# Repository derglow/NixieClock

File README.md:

# NixieClock

This repository contains the files used to make my nixie clock design. I designed the PCBs, the laser cut acrylic, and wrote the code.

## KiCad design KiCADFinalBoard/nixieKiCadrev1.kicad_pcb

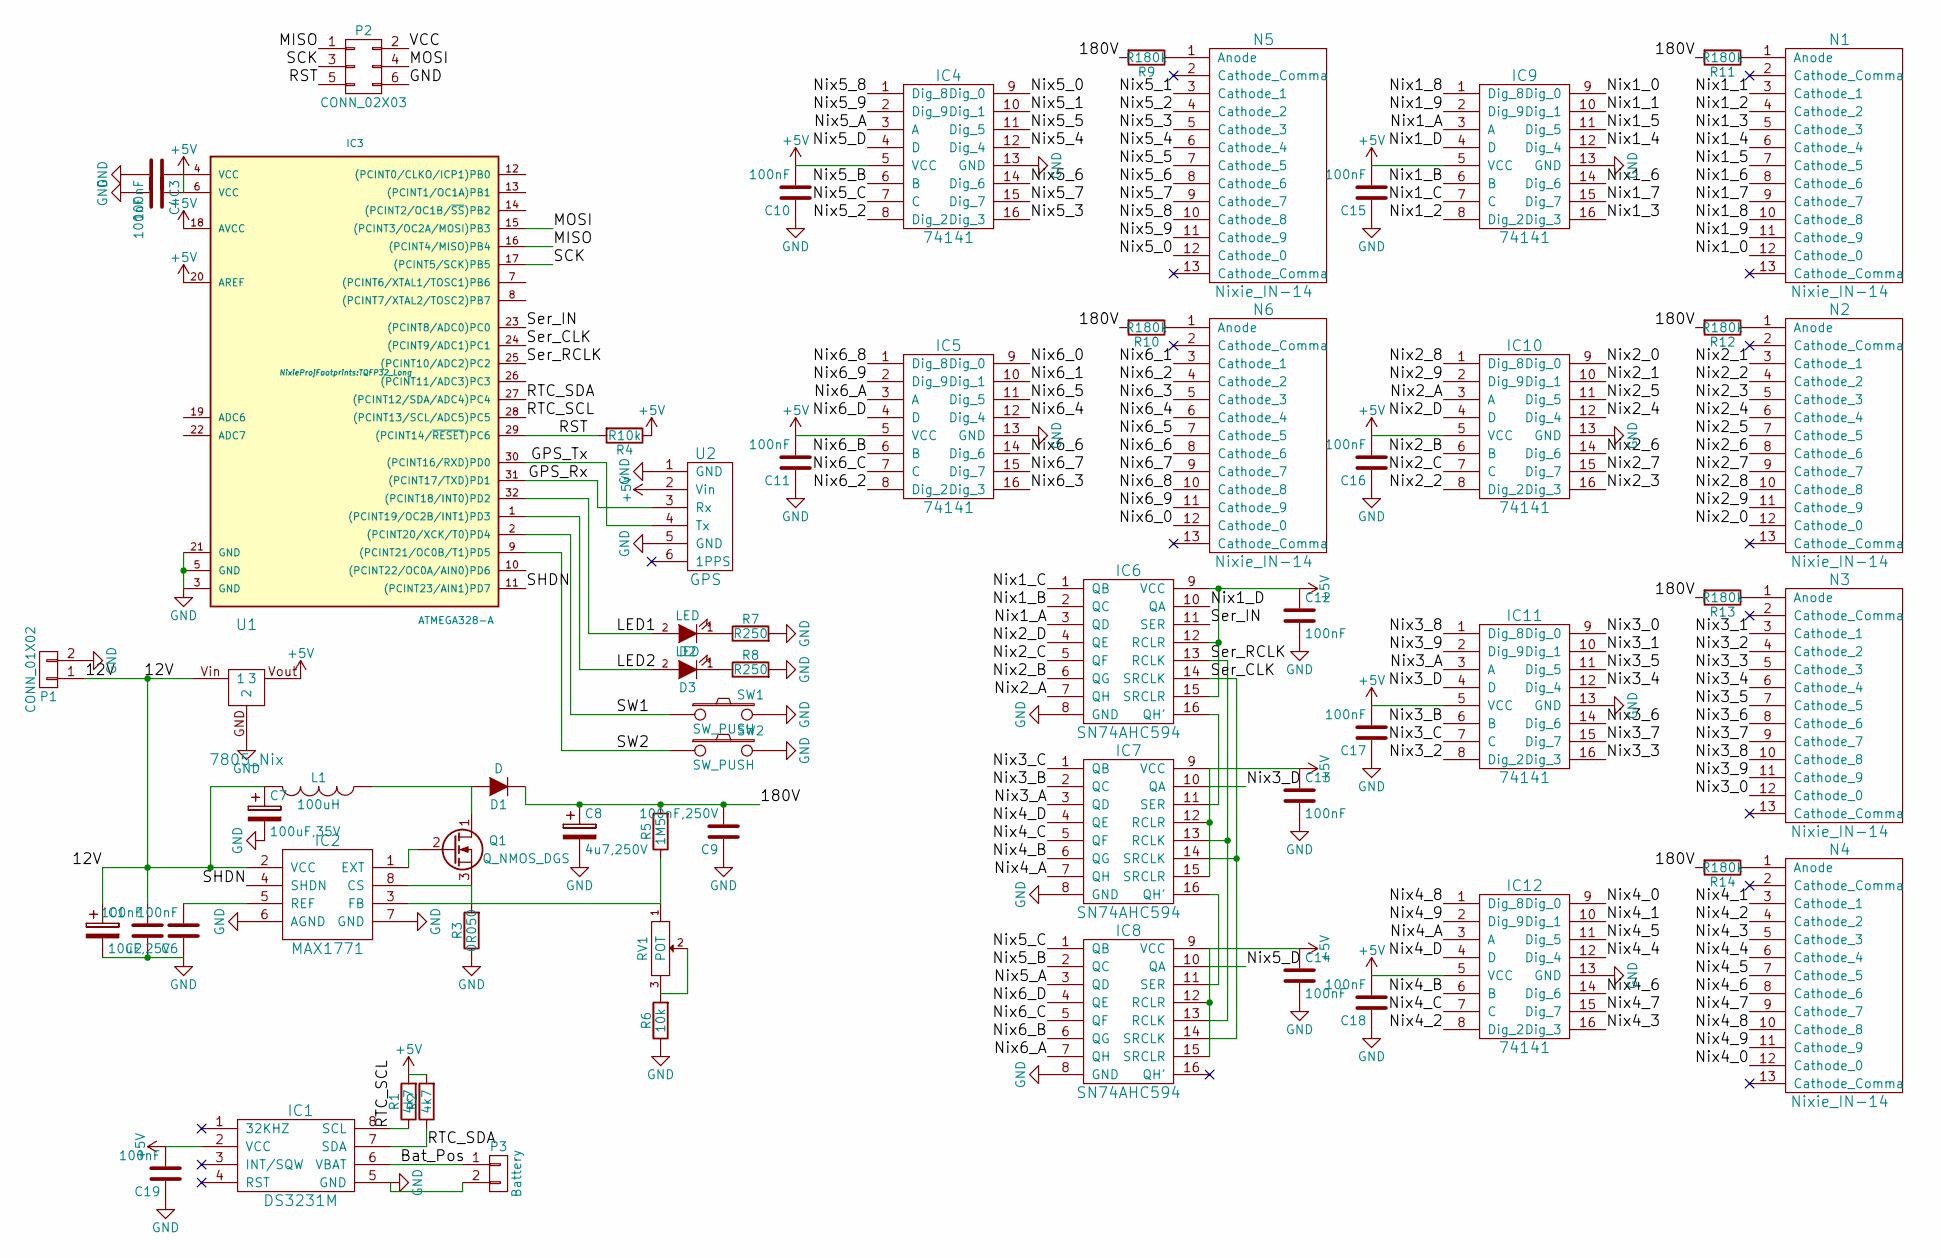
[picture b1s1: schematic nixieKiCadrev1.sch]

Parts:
C1: 10uF,25V; TantalC_SizeC_EIA-6032_HandSoldering
C2, C3, C4, C6, C10, C11, C12, C13, C14, C15, C16, C17, C18, C19: 100nF; C_0805_HandSoldering
C7: 100uF,35V; TantalC_SizeE_EIA-7360_HandSoldering
C8: 4u7,250V; c_elec_10x10
C9: 100nF,250V; C_2220_HandSoldering
D1: D; Diode-MELF_Handsoldering
D2, D3: LED; LED-0805
IC1: DS3231M; SOIC-8-N
IC2: MAX1771; SOIC-8-N
IC3: ATMEGA328-A; TQFP32_Long
IC4, IC5, IC9, IC10, IC11, IC12: 74141; DIP-16_W7.62mm_LongPads
IC6, IC7, IC8: SN74AHC594; TSSOP-16_4.4x5mm_Pitch0.65mm
L1: 100uH; Inductor
N1, N2, N3, N4, N5, N6: Nixie_IN-14; Nixie_IN14
P1: CONN_01X02; BARREL_JACK
P2: CONN_02X03; Pin_Header_Straight_2x03
P3: Battery; CR2032_BatHolder
Q1: Q_NMOS_DGS; TO-220_Neutral123_Vertical
R1, R2: 4k7; R_0805_HandSoldering
R3: 0R050; R_2512_HandSoldering
R4: R10k; R_0805_HandSoldering
R5: 1M5; R_2512_HandSoldering
R6: 10k; R_0805_HandSoldering
R7, R8: R250; R_0805_HandSoldering
R9, R10, R11, R12, R13, R14: R180k; R_0805_HandSoldering
RV1: POT; TrimPot
SW1, SW2: SW_PUSH; SW_SPST_PTS645
U1: 7805_Nix; TO-220_Neutral123_Vertical
U2: GPS; EM406gps

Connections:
+5V: C3.1, C4.1, C10.2, C11.2, C12.1, C13.1, C14.1, C15.2, C16.2, C17.2, C18.2, C19.2, IC1.2 (VCC), IC3.4 (VCC), IC3.6 (VCC), IC3.18 (AVCC), IC3.20 (AREF), IC4.5 (VCC), IC5.5 (VCC), IC6.9 (VCC), IC6.12 (RCLR), IC6.15 (SRCLR), IC7.9 (VCC), IC7.12 (RCLR), IC7.15 (SRCLR), IC8.9 (VCC), IC8.12 (RCLR), IC8.15 (SRCLR), IC9.5 (VCC), IC10.5 (VCC), IC11.5 (VCC), IC12.5 (VCC), R1.2, R2.2, R4.1, U1.3, U1.Vout (3), U2.2 (Vin)
/12V: C1.1, C2.2, C7.1, IC2.2 (VCC), L1.2, P1.1, U1.1, U1.Vin (1)
/180V: C8.1, C9.2, D1.1 (K), R5.2, R9.2, R10.2, R11.2, R12.2, R13.2, R14.2
/Bat_Pos: IC1.6 (VBAT), P3.1
/GPS_Rx: IC3.31 ((PCINT17/TXD)PD1), U2.3 (Rx)
/GPS_Tx: IC3.30 ((PCINT16/RXD)PD0), U2.4 (Tx)
/LED1: D2.2 (A), IC3.32 ((PCINT18/INT0)PD2)
/LED2: D3.2 (A), IC3.1 ((PCINT19/OC2B/INT1)PD3)
/MISO: IC3.16 ((PCINT4/MISO)PB4), P2.1
/MOSI: IC3.15 ((PCINT3/OC2A/MOSI)PB3), P2.4
/Nix1_0: IC9.9 (Dig_0), N1.12 (Cathode_0)
/Nix1_1: IC9.10 (Dig_1), N1.3 (Cathode_1)
/Nix1_2: IC9.8 (Dig_2), N1.4 (Cathode_2)
/Nix1_3: IC9.16 (Dig_3), N1.5 (Cathode_3)
/Nix1_4: IC9.12 (Dig_4), N1.6 (Cathode_4)
/Nix1_5: IC9.11 (Dig_5), N1.7 (Cathode_5)
/Nix1_6: IC9.14 (Dig_6), N1.8 (Cathode_6)
/Nix1_7: IC9.15 (Dig_7), N1.9 (Cathode_7)
/Nix1_8: IC9.1 (Dig_8), N1.10 (Cathode_8)
/Nix1_9: IC9.2 (Dig_9), N1.11 (Cathode_9)
/Nix1_A: IC6.3 (QD), IC9.3 (A)
/Nix1_B: IC6.2 (QC), IC9.6 (B)
/Nix1_C: IC6.1 (QB), IC9.7 (C)
/Nix1_D: IC6.10 (QA), IC9.4 (D)
/Nix2_0: IC10.9 (Dig_0), N2.12 (Cathode_0)
/Nix2_1: IC10.10 (Dig_1), N2.3 (Cathode_1)
/Nix2_2: IC10.8 (Dig_2), N2.4 (Cathode_2)
/Nix2_3: IC10.16 (Dig_3), N2.5 (Cathode_3)
/Nix2_4: IC10.12 (Dig_4), N2.6 (Cathode_4)
/Nix2_5: IC10.11 (Dig_5), N2.7 (Cathode_5)
/Nix2_6: IC10.14 (Dig_6), N2.8 (Cathode_6)
/Nix2_7: IC10.15 (Dig_7), N2.9 (Cathode_7)
/Nix2_8: IC10.1 (Dig_8), N2.10 (Cathode_8)
/Nix2_9: IC10.2 (Dig_9), N2.11 (Cathode_9)
/Nix2_A: IC6.7 (QH), IC10.3 (A)
/Nix2_B: IC6.6 (QG), IC10.6 (B)
/Nix2_C: IC6.5 (QF), IC10.7 (C)
/Nix2_D: IC6.4 (QE), IC10.4 (D)
/Nix3_0: IC11.9 (Dig_0), N3.12 (Cathode_0)
/Nix3_1: IC11.10 (Dig_1), N3.3 (Cathode_1)
/Nix3_2: IC11.8 (Dig_2), N3.4 (Cathode_2)
/Nix3_3: IC11.16 (Dig_3), N3.5 (Cathode_3)
/Nix3_4: IC11.12 (Dig_4), N3.6 (Cathode_4)
/Nix3_5: IC11.11 (Dig_5), N3.7 (Cathode_5)
/Nix3_6: IC11.14 (Dig_6), N3.8 (Cathode_6)
/Nix3_7: IC11.15 (Dig_7), N3.9 (Cathode_7)
/Nix3_8: IC11.1 (Dig_8), N3.10 (Cathode_8)
/Nix3_9: IC11.2 (Dig_9), N3.11 (Cathode_9)
/Nix3_A: IC7.3 (QD), IC11.3 (A)
/Nix3_B: IC7.2 (QC), IC11.6 (B)
/Nix3_C: IC7.1 (QB), IC11.7 (C)
/Nix3_D: IC7.10 (QA), IC11.4 (D)
/Nix4_0: IC12.9 (Dig_0), N4.12 (Cathode_0)
/Nix4_1: IC12.10 (Dig_1), N4.3 (Cathode_1)
/Nix4_2: IC12.8 (Dig_2), N4.4 (Cathode_2)
/Nix4_3: IC12.16 (Dig_3), N4.5 (Cathode_3)
/Nix4_4: IC12.12 (Dig_4), N4.6 (Cathode_4)
/Nix4_5: IC12.11 (Dig_5), N4.7 (Cathode_5)
/Nix4_6: IC12.14 (Dig_6), N4.8 (Cathode_6)
/Nix4_7: IC12.15 (Dig_7), N4.9 (Cathode_7)
/Nix4_8: IC12.1 (Dig_8), N4.10 (Cathode_8)
/Nix4_9: IC12.2 (Dig_9), N4.11 (Cathode_9)
/Nix4_A: IC7.7 (QH), IC12.3 (A)
/Nix4_B: IC7.6 (QG), IC12.6 (B)
/Nix4_C: IC7.5 (QF), IC12.7 (C)
/Nix4_D: IC7.4 (QE), IC12.4 (D)
/Nix5_0: IC4.9 (Dig_0), N5.12 (Cathode_0)
/Nix5_1: IC4.10 (Dig_1), N5.3 (Cathode_1)
/Nix5_2: IC4.8 (Dig_2), N5.4 (Cathode_2)
/Nix5_3: IC4.16 (Dig_3), N5.5 (Cathode_3)
/Nix5_4: IC4.12 (Dig_4), N5.6 (Cathode_4)
/Nix5_5: IC4.11 (Dig_5), N5.7 (Cathode_5)
/Nix5_6: IC4.14 (Dig_6), N5.8 (Cathode_6)
/Nix5_7: IC4.15 (Dig_7), N5.9 (Cathode_7)
/Nix5_8: IC4.1 (Dig_8), N5.10 (Cathode_8)
/Nix5_9: IC4.2 (Dig_9), N5.11 (Cathode_9)
/Nix5_A: IC4.3 (A), IC8.3 (QD)
/Nix5_B: IC4.6 (B), IC8.2 (QC)
/Nix5_C: IC4.7 (C), IC8.1 (QB)
/Nix5_D: IC4.4 (D), IC8.10 (QA)
/Nix6_0: IC5.9 (Dig_0), N6.12 (Cathode_0)
/Nix6_1: IC5.10 (Dig_1), N6.3 (Cathode_1)
/Nix6_2: IC5.8 (Dig_2), N6.4 (Cathode_2)
/Nix6_3: IC5.16 (Dig_3), N6.5 (Cathode_3)
/Nix6_4: IC5.12 (Dig_4), N6.6 (Cathode_4)
/Nix6_5: IC5.11 (Dig_5), N6.7 (Cathode_5)
/Nix6_6: IC5.14 (Dig_6), N6.8 (Cathode_6)
/Nix6_7: IC5.15 (Dig_7), N6.9 (Cathode_7)
/Nix6_8: IC5.1 (Dig_8), N6.10 (Cathode_8)
/Nix6_9: IC5.2 (Dig_9), N6.11 (Cathode_9)
/Nix6_A: IC5.3 (A), IC8.7 (QH)
/Nix6_B: IC5.6 (B), IC8.6 (QG)
/Nix6_C: IC5.7 (C), IC8.5 (QF)
/Nix6_D: IC5.4 (D), IC8.4 (QE)
/RST: IC3.29 ((PCINT14/~RESET~)PC6), P2.5, R4.2
/RTC_SCL: IC1.8 (SCL), IC3.28 ((PCINT13/SCL/ADC5)PC5), R1.1
/RTC_SDA: IC1.7 (SDA), IC3.27 ((PCINT12/SDA/ADC4)PC4), R2.1
/SCK: IC3.17 ((PCINT5/SCK)PB5), P2.3
/SHDN: IC2.4 (SHDN), IC3.11 ((PCINT23/AIN1)PD7)
/SW1: IC3.2 ((PCINT20/XCK/T0)PD4), SW1.1
/SW2: IC3.9 ((PCINT21/OC0B/T1)PD5), SW2.1
/Ser_CLK: IC3.24 ((PCINT9/ADC1)PC1), IC6.14 (SRCLK), IC7.14 (SRCLK), IC8.14 (SRCLK)
/Ser_IN: IC3.23 ((PCINT8/ADC0)PC0), IC6.11 (SER)
/Ser_RCLK: IC3.25 ((PCINT10/ADC2)PC2), IC6.13 (RCLK), IC7.13 (RCLK), IC8.13 (RCLK)
/VCC: P2.2
GND: C1.2, C2.1, C3.2, C4.2, C6.1, C7.2, C8.2, C9.1, C10.1, C11.1, C12.2, C13.2, C14.2, C15.1, C16.1, C17.1, C18.1, C19.1, IC1.5 (GND), IC2.6 (AGND), IC2.7 (GND), IC3.3 (GND), IC3.5 (GND), IC3.21 (GND), IC4.13 (GND), IC5.13 (GND), IC6.8 (GND), IC7.8 (GND), IC8.8 (GND), IC9.13 (GND), IC10.13 (GND), IC11.13 (GND), IC12.13 (GND), P1.2, P2.6, P3.2, R3.1, R6.1, R7.2, R8.2, SW1.2, SW2.2, U1.2, U1.GND (2), U2.1 (GND), U2.5 (GND)
unnamed: C6.2, IC2.5 (REF)
unnamed: D1.2 (A), L1.1, Q1.1 (D)
unnamed: D2.1 (K), R7.1
unnamed: D3.1 (K), R8.1
unnamed: IC2.1 (EXT), Q1.2 (G)
unnamed: IC2.3 (FB), R5.1, RV1.1
unnamed: IC2.8 (CS), Q1.3 (S), R3.2
unnamed: IC6.16 (QH'), IC7.11 (SER)
unnamed: IC7.16 (QH'), IC8.11 (SER)
unnamed: N1.1 (Anode), R11.1
unnamed: N2.1 (Anode), R12.1
unnamed: N3.1 (Anode), R13.1
unnamed: N4.1 (Anode), R14.1
unnamed: N5.1 (Anode), R9.1
unnamed: N6.1 (Anode), R10.1
unnamed: R6.2, RV1.2, RV1.3

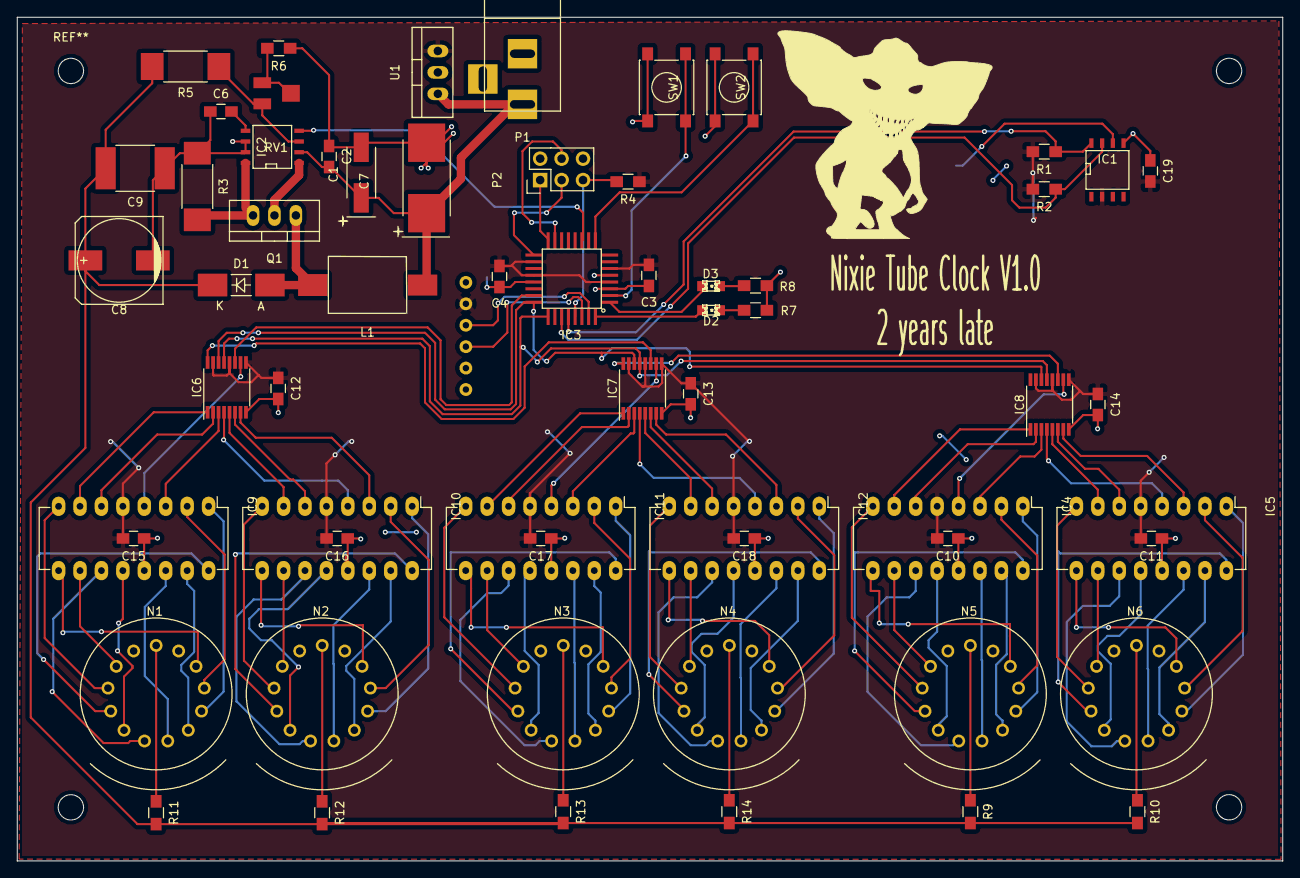
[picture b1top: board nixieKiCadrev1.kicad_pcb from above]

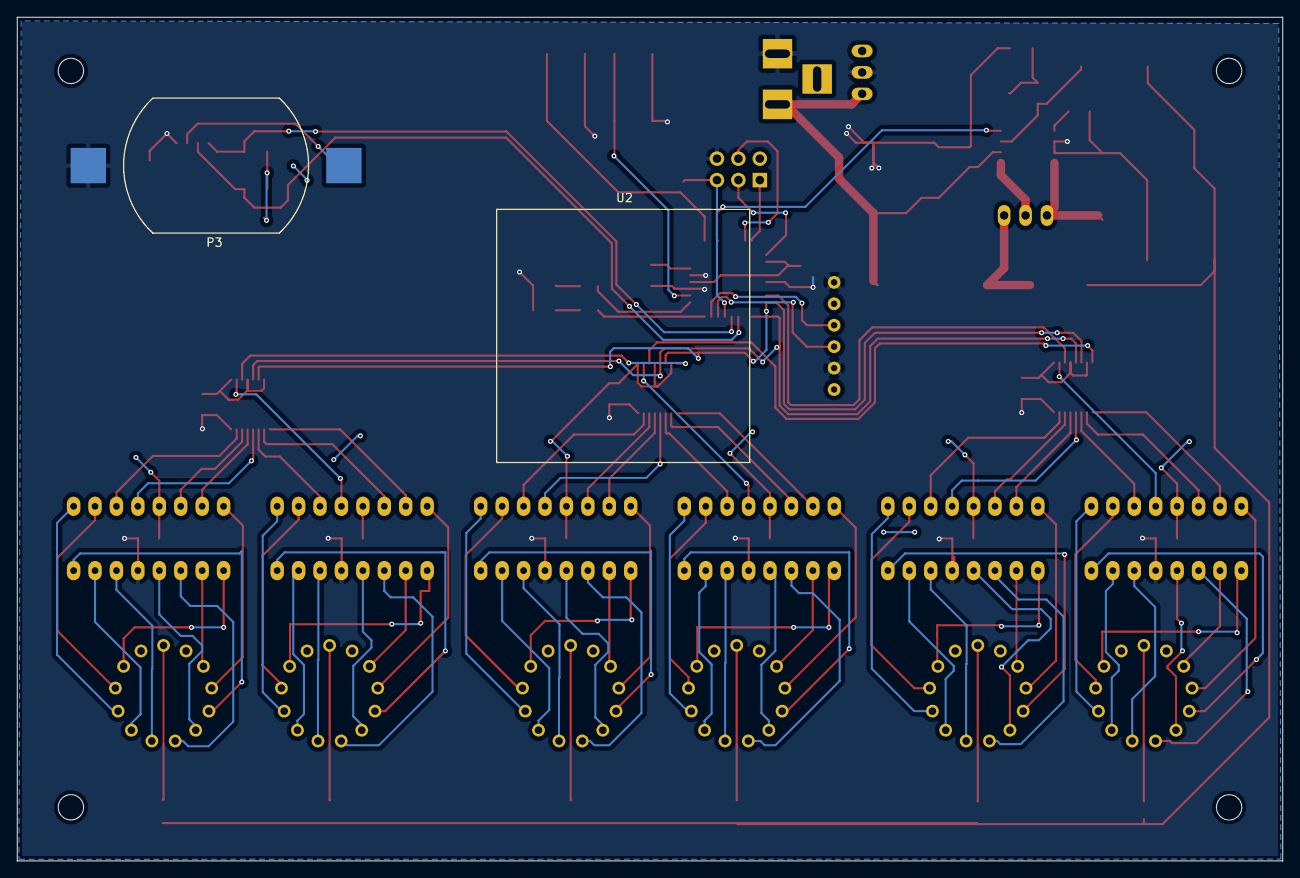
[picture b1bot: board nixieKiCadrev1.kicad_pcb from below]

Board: 2 copper layers, 150.0 x 100.0 mm, 63 parts (2 on the bottom side), 121 nets.

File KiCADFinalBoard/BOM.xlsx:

|  | value | ref | value5 | footprint | lib | part | DigiKey PN | Column1
 |  |  | C1 | 10uF,25V | Capacitors_Tantalum_SMD:TantalC_SizeC_EIA-6032_HandSoldering | device | CP | 718-1098-1-ND
 |  |  | C10 | 100nF | Capacitors_SMD:C_0805_HandSoldering | device | C | 1276-1007-1-ND
 |  |  | C11 | 100nF | Capacitors_SMD:C_0805_HandSoldering | device | C | 1276-1007-1-ND
 |  |  | C12 | 100nF | Capacitors_SMD:C_0805_HandSoldering | device | C | 1276-1007-1-ND
 |  |  | C13 | 100nF | Capacitors_SMD:C_0805_HandSoldering | device | C | 1276-1007-1-ND
 |  |  | C14 | 100nF | Capacitors_SMD:C_0805_HandSoldering | device | C | 1276-1007-1-ND
 |  |  | C15 | 100nF | Capacitors_SMD:C_0805_HandSoldering | device | C | 1276-1007-1-ND
 |  |  | C16 | 100nF | Capacitors_SMD:C_0805_HandSoldering | device | C | 1276-1007-1-ND
 |  |  | C17 | 100nF | Capacitors_SMD:C_0805_HandSoldering | device | C | 1276-1007-1-ND
 |  |  | C18 | 100nF | Capacitors_SMD:C_0805_HandSoldering | device | C | 1276-1007-1-ND
 |  |  | C19 | 100nF | Capacitors_SMD:C_0805_HandSoldering | device | C | 1276-1007-1-ND
 |  |  | C2 | 100nF | Capacitors_SMD:C_0805_HandSoldering | device | C | 1276-1007-1-ND
 |  |  | C3 | 100nF | Capacitors_SMD:C_0805_HandSoldering | device | C | 1276-1007-1-ND
 |  |  | C4 | 100nF | Capacitors_SMD:C_0805_HandSoldering | device | C | 1276-1007-1-ND
 |  |  | C6 | 100nF | Capacitors_SMD:C_0805_HandSoldering | device | C | 1276-1007-1-ND
 |  |  | C7 | 100uF,35V | Capacitors_Tantalum_SMD:TantalC_SizeE_EIA-7360_HandSoldering | device | CP | 718-1774-1-ND
 |  |  | C8 | 4u7,250V | Capacitors_SMD:c_elec_10x10 | device | CP | PCE3432CT-ND
 |  |  | C9 | 100nF,250V | Capacitors_SMD:C_2220_HandSoldering | device | C | 399-5481-1-ND
 |  |  | D1 | D | Diodes_SMD:Diode-MELF_Handsoldering | device | D | ES2F-E3/52TGICT-ND
 |  |  | D2 | LED | LEDs:LED-0805 | device | LED | NA
 |  |  | D3 | LED | LEDs:LED-0805 | device | LED | NA
 |  |  | IC1 | DS3231M | SMD_Packages:SOIC-8-N | NixieBoardKiCAD | DS3231M | DS3231MZ+-ND
 |  |  | IC10 | 74141 | Housings_DIP:DIP-16_W7.62mm_LongPads | NixieBoardKiCAD | 74141 | NA
 |  |  | IC11 | 74141 | Housings_DIP:DIP-16_W7.62mm_LongPads | NixieBoardKiCAD | 74141 | NA
 |  |  | IC12 | 74141 | Housings_DIP:DIP-16_W7.62mm_LongPads | NixieBoardKiCAD | 74141 | NA
 |  |  | IC2 | MAX1771 | SMD_Packages:SOIC-8-N | NixieBoardKiCAD | MAX1771 | MAX1771CSA+-ND
 |  |  | IC3 | ATMEGA328-A | NixieProjFootprints:TQFP32_Long | atmel | ATMEGA328-A | ATMEGA328P-AU-ND
 |  |  | IC4 | 74141 | Housings_DIP:DIP-16_W7.62mm_LongPads | NixieBoardKiCAD | 74141 | NA
 |  |  | IC5 | 74141 | Housings_DIP:DIP-16_W7.62mm_LongPads | NixieBoardKiCAD | 74141 | NA
 |  |  | IC6 | SN74AHC594 | Housings_SSOP:TSSOP-16_4.4x5mm_Pitch0.65mm | NixieBoardKiCAD | SN74AHC594 | 296-4620-1-ND
 |  |  | IC7 | SN74AHC594 | Housings_SSOP:TSSOP-16_4.4x5mm_Pitch0.65mm | NixieBoardKiCAD | SN74AHC594 | 296-4620-1-ND
 |  |  | IC8 | SN74AHC594 | Housings_SSOP:TSSOP-16_4.4x5mm_Pitch0.65mm | NixieBoardKiCAD | SN74AHC594 | 296-4620-1-ND
 |  |  | IC9 | 74141 | Housings_DIP:DIP-16_W7.62mm_LongPads | NixieBoardKiCAD | 74141 | NA
 |  |  | L1 | 100uH | NixieProjFootprints:Inductor | device | INDUCTOR | M8603CT-ND
 |  |  | N1 | Nixie_IN-14 | NixieProjFootprints:Nixie_IN14 | nixieKiCadrev1-cache | Nixie_IN-14 | NA
 |  |  | N2 | Nixie_IN-14 | NixieProjFootprints:Nixie_IN14 | nixieKiCadrev1-cache | Nixie_IN-14 | NA
 |  |  | N3 | Nixie_IN-14 | NixieProjFootprints:Nixie_IN14 | nixieKiCadrev1-cache | Nixie_IN-14 | NA
 |  |  | N4 | Nixie_IN-14 | NixieProjFootprints:Nixie_IN14 | nixieKiCadrev1-cache | Nixie_IN-14 | NA
 |  |  | N5 | Nixie_IN-14 | NixieProjFootprints:Nixie_IN14 | nixieKiCadrev1-cache | Nixie_IN-14 | NA
 |  |  | N6 | Nixie_IN-14 | NixieProjFootprints:Nixie_IN14 | nixieKiCadrev1-cache | Nixie_IN-14 | NA
 |  |  | P1 | CONN_01X02 | Connect:BARREL_JACK | conn | CONN_01X02 | NA
 |  |  | P2 | CONN_02X03 | Pin_Headers:Pin_Header_Straight_2x03 | conn | CONN_02X03 | NA
 |  |  | P3 | Battery | NixieProjFootprints:CR2032_BatHolder | conn | CONN_01X02 | NA
 |  |  | Q1 | Q_NMOS_DGS | TO_SOT_Packages_THT:TO-220_Neutral123_Vertical | device | Q_NMOS_DGS | IRF644PBF-ND
 |  |  | R1 | 4k7 | Resistors_SMD:R_0805_HandSoldering | device | R | 311-4.7KARCT-ND
 |  |  | R10 | R180k | Resistors_SMD:R_0805_HandSoldering | device | R | 311-180KARCT-ND | 311-100KARCT-ND
 |  |  | R11 | R180k | Resistors_SMD:R_0805_HandSoldering | device | R | 311-180KARCT-ND | 311-100KARCT-ND
 |  |  | R12 | R180k | Resistors_SMD:R_0805_HandSoldering | device | R | 311-180KARCT-ND | 311-100KARCT-ND
 |  |  | R13 | R180k | Resistors_SMD:R_0805_HandSoldering | device | R | 311-180KARCT-ND | 311-100KARCT-ND
 |  |  | R14 | R180k | Resistors_SMD:R_0805_HandSoldering | device | R | 311-180KARCT-ND | 311-100KARCT-ND
 |  |  | R2 | 4k7 | Resistors_SMD:R_0805_HandSoldering | device | R | 311-4.7KARCT-ND
 |  |  | R3 | 0R050 | Resistors_SMD:R_2512_HandSoldering | device | R | 985-1555-1-ND
 |  |  | R4 | R10k | Resistors_SMD:R_0805_HandSoldering | device | R | 311-10KARCT-ND
 |  |  | R5 | 1M5 | Resistors_SMD:R_2512_HandSoldering | device | R | PT1.5MXCT-ND
 |  |  | R6 | 10k | Resistors_SMD:R_0805_HandSoldering | device | R | 311-10KARCT-ND
 |  |  | R7 | R250 | Resistors_SMD:R_0805_HandSoldering | device | R | 311-240ARCT-ND
 |  |  | R8 | R250 | Resistors_SMD:R_0805_HandSoldering | device | R | 311-240ARCT-ND
 |  |  | R9 | R180k | Resistors_SMD:R_0805_HandSoldering | device | R | 311-180KARCT-ND | 311-100KARCT-ND
 |  |  | RV1 | POT | NixieProjFootprints:TrimPot | device | POT | P3V502CT-ND
 |  |  | SW1 | SW_PUSH | Buttons_Switches_SMD:SW_SPST_PTS645 | device | SW_PUSH | 450-1129-ND
 |  |  | SW2 | SW_PUSH | Buttons_Switches_SMD:SW_SPST_PTS645 | device | SW_PUSH | 450-1129-ND
 |  |  | U1 | 7805_Nix | TO_SOT_Packages_THT:TO-220_Neutral123_Vertical | NixieBoardKiCAD | 7805_Nix | NA
 |  |  | U2 | GPS | NixieProjFootprints:EM406gps | NixieBoardKiCAD | GPS | NA

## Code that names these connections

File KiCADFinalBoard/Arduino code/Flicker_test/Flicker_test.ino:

//Define all the pins//
#define serData 14 //PC0 A0=14
#define serClk 15 //PC1 A1=15
#define serRClk 16 //PC2 A2=16

#define led1 2 //PD2
#define led2 3 //PD3

#define switch1 4 //portD 
#define switch2 5 //portD

#define supplyShtdn 7 //PD7

//Serial related variables//
#define serialBufferLength 80
uint8_t receivedByte;
uint8_t serialReceiveBuffer[serialBufferLength];
uint8_t serialReceivePos = 0;
uint8_t processReceivedByte = 0;

uint8_t GPShourDig1;
uint8_t GPShourDig2;
uint8_t GPSminuteDig1;
uint8_t GPSminuteDig2;
uint8_t GPSsecondDig1;
uint8_t GPSsecondDig2;

//Define the proper shift register output for each digit//
uint8_t decadeValues[11] = {
  0b00000000, //this decodes to digit 0
  0b00000001, //this decodes to digit 1
  0b00000010, //this decodes to digit 2
  0b00000011, //this decodes to digit 3
  0b00000100, //this decodes to digit 4
  0b00000101, //this decodes to digit 5
  0b00000110, //this decodes to digit 6
  0b00000111, //this decodes to digit 7
  0b00001000, //this decodes to digit 8
  0b00001001, //this decodes to digit 9
  0b00001111, //this decodes to no digit
};

void setup() {
  pinMode(supplyShtdn,OUTPUT);
  digitalWrite(supplyShtdn,LOW);

  pinMode(led1,OUTPUT);
  pinMode(led2,OUTPUT);
  
  pinMode(serData,OUTPUT);
  pinMode(serClk,OUTPUT);
  pinMode(serRClk,OUTPUT);

  sendSixDigits(0,0,0,0,0,0);
  delay(100);  
  sendSixDigits(1,1,1,1,1,1);
  delay(100);  
  sendSixDigits(2,2,2,2,2,2);
  delay(100);  
  sendSixDigits(3,3,3,3,3,3);
  delay(100);  
  sendSixDigits(4,4,4,4,4,4);
  delay(100);  
  sendSixDigits(5,5,5,5,5,5);
  delay(100);  
  sendSixDigits(6,6,6,6,6,6);
  delay(100);  
  sendSixDigits(7,7,7,7,7,7);
  delay(100);  
  sendSixDigits(8,8,8,8,8,8);
  delay(100);  
  sendSixDigits(9,9,9,9,9,9);
  delay(100);
  sendSixDigits(10,10,10,10,10,10);
  Serial.begin(4800);
}


byte perc=5;
#define minPerc 3 //3 goes with 17,5 goes with 30
#define maxPerc 10
#define numCycles 17 //3 goes with 17, 5 goes with 30
byte ticker1=0;
byte ticker2=0;
byte ticker3=0;

void loop() {

  if(ticker1<perc){
    sendSixDigits(ticker3,ticker3,ticker3,ticker3,ticker3,ticker3);
    ticker1++;
  }
  else{
    sendSixDigits(10,10,10,10,10,10);
    ticker1++;
  }
  if(ticker1>=maxPerc){
    ticker1=0;
    ticker2++;
  }
  if(ticker2>=numCycles){
    perc++;
    if(perc>=maxPerc){
      perc=minPerc;
    ticker3++;
    }
    ticker2=0;
  }
    if(ticker3>=10){
      ticker3=0;
    }
}

uint8_t asciiToBin(uint8_t asciiValue){ //converts ascii to bin, if outside of 0-9 range it returns 10
  if((asciiValue >= 0x30) & (asciiValue <= 0x39)){
    return (asciiValue - 0x30);
  }
  else{
    return 10;
  }
}

void storeTime(void){
  GPShourDig1 = asciiToBin(serialReceiveBuffer[7]);
  GPShourDig2 = asciiToBin(serialReceiveBuffer[8]);
  GPSminuteDig1 = asciiToBin(serialReceiveBuffer[9]);
  GPSminuteDig2 = asciiToBin(serialReceiveBuffer[10]);
  GPSsecondDig1 = asciiToBin(serialReceiveBuffer[11]);
  GPSsecondDig2 = asciiToBin(serialReceiveBuffer[12]);
}

void processReceivedByteFn(void){
  if(processReceivedByte==1){ //Check serial flag
    if(receivedByte==36){ //Check for $
      serialReceivePos=0; //reset to position 0
      serialReceiveBuffer[serialReceivePos]=receivedByte; //add the $ to pos 0 (unnecessary command)
      serialReceivePos++; //increment the position
      processReceivedByte=0;      //clear the flag
    }
    else{//all other received bytes
      //add the byte to buffer, then increment the pos, check if the pos is overflowed 
      serialReceiveBuffer[serialReceivePos]=receivedByte;
      serialReceivePos++; //increment the position
      if(serialReceivePos==80){
        serialReceivePos=79;
      }
      if((receivedByte == 0x0D) & (serialReceiveBuffer[3] == 0x47) & (serialReceiveBuffer[4] == 0x47) & (serialReceiveBuffer[5] == 0x41)){//if received byte is carriage return and GPGGA is found, save the time
        storeTime();
        sendSixDigits(GPShourDig1,GPShourDig2,GPSminuteDig1,GPSminuteDig2,GPSsecondDig1,GPSsecondDig2);
      }
      processReceivedByte=0; //clear the flag
    }
  }
}

void flashLED1(uint8_t delayTime){
  digitalWrite(led1,HIGH);
  delay(delayTime);
  digitalWrite(led1,LOW);
}

void flashLED2(uint8_t delayTime){
  digitalWrite(led2,HIGH);
  delay(delayTime);
  digitalWrite(led2,LOW);
}

void sendSixDigits(uint8_t hour1, uint8_t hour2, uint8_t minute1, uint8_t minute2, uint8_t second1,uint8_t second2){
  uint8_t sendThisByte3 = ((decadeValues[second1]<<4)|decadeValues[second2]);
  uint8_t sendThisByte2 = ((decadeValues[minute1]<<4)|decadeValues[minute2]);
  uint8_t sendThisByte1 = ((decadeValues[hour1]<<4)|decadeValues[hour2]);
  for(uint8_t x = 0; x < 8; x += 1){
    if((sendThisByte3 >> x) & 0x01){
        digitalWrite(serData,HIGH);
    }
    else{
        digitalWrite(serData,LOW);
    }
  digitalWrite(serClk,HIGH);
  digitalWrite(serClk,LOW);
  }

    for(uint8_t x = 0; x < 8; x += 1){
    if((sendThisByte2 >> x) & 0x01){
        digitalWrite(serData,HIGH);
    }
    else{
        digitalWrite(serData,LOW);
    }
  digitalWrite(serClk,HIGH);
  digitalWrite(serClk,LOW);
  }

    for(uint8_t x = 0; x < 8; x += 1){
    if((sendThisByte1 >> x) & 0x01){
        digitalWrite(serData,HIGH);
    }
    else{
        digitalWrite(serData,LOW);
    }
  digitalWrite(serClk,HIGH);
  digitalWrite(serClk,LOW);
  }
  
  digitalWrite(serRClk,HIGH);
  digitalWrite(serRClk,LOW);
}

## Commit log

2018-04-29 Rename Rev2.ino to Code.ino
